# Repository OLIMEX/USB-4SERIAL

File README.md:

# USB-4SERIAL

USB-4SERIAL is Open Source Harrdware USB 2.0 High Speed to four RS232 levels or 3.3V TTL levels serial UARTs and one shared RS485 current loop serial port

## Features
* USB-C High Speed USB 2.0 connector for powering the board and communication
* The serial ports can be with baud rate up to 12Mbps on the TTL connector and up to 115200 bpx on RS232 levels connectors.
* The serial ports are compatible with 16C550 UART and support 5, 6, 7 or 8 data bits and 1 or 2 stop bits, odd, even, none, blank0, mark1 and other parity.
* Supports RTS and CTS hardware automatic flow control for the First one RS232 Serial port.
* Supports half-duplex and RS485 switching for the Fourth port.
* RS485 direction flow selectable by RTS3 or GPIO11
* Reset button
* High reliable industrial grade design -40+85C
* CE-RED and LVD certification
* Four mount holes 3 mm
* PCB dimensions: (150 x 35)mm ~ (5.9 x 1.38)"

Product page: https://www.olimex.com/Products/USB-Modules/USB-4SERIAL/open-source-hardware

## Licensee
* Hardware is released under CERN Open Hardware Licence Version 2 - Strongly Reciprocal, all silkscreen credits to Olimex should remain;
* Software is released under GPL3 Licensee
* Documentation is released under CC BY-SA 3.0

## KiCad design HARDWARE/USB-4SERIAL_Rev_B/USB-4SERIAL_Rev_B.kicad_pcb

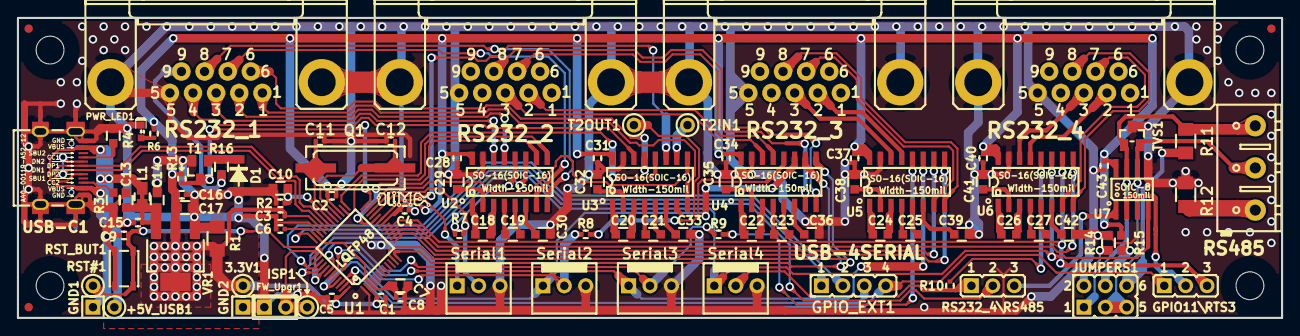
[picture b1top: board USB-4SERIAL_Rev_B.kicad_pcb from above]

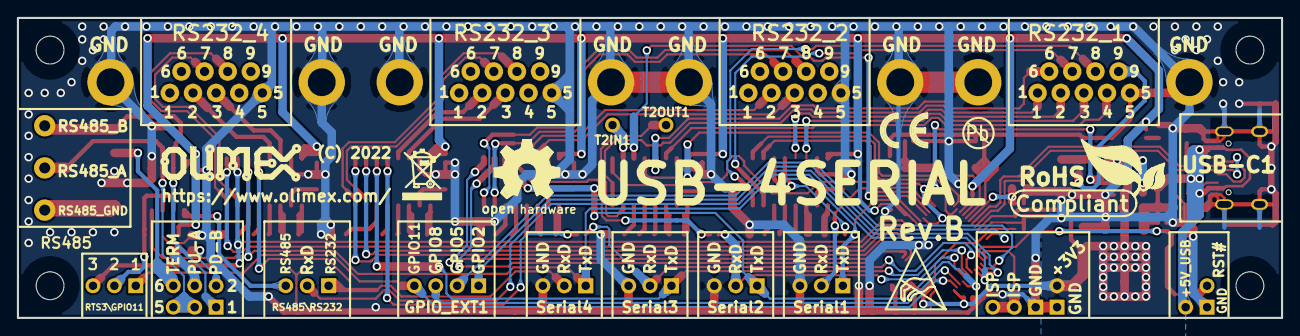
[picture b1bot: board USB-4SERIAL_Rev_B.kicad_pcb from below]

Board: 2 copper layers, 149.9 x 35.6 mm, 111 parts (7 on the bottom side), 104 nets.

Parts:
3.3V1: TESTPAD; TP_PTH-CIRCLE
+5V_USB1: TESTPAD; TP_PTH-CIRCLE
C1, C2, C3, C4, C5, C6, C9, C15, C16, C28, C31, C34, C37, C40, C43: 100nF/10V/10%/X7R/C0402; C_0402_5MIL_DWS
C7: 1uF/10V/10%/X5R/C0603; C_0603_5MIL_DWS
C8: 2.2uF/6.3V/20%/X5R/C0402; C_0402_5MIL_DWS
C10: 20pF/50V/5%/C0G/C0603; C_0603_5MIL_DWS
C11, C12: 39pF/50V/5%/C0G/C0402; C_0402_5MIL_DWS
C13: NA(22uF/6.3V/20%/X5R/C0603); C_0603_5MIL_DWS
C14, C17: 22uF/6.3V/20%/X5R/C0603; C_0603_5MIL_DWS
C18, C19, C20, C21, C22, C23, C24, C25, C26, C27, C29, C30, C32, C33, C35, C36, C38, C39, C41, C42: 100nF/50V/20%/Y5V/C0603; C_0603_5MIL_DWS
D1: 1N5819S4(SOD-123); SOD-123_1C-2A_KA
FID1, FID2, FID3: Fiducial; Fiducial1x3
FW_Upgr1: NA(HN1x2); HN1x2_Jumper
GND1, GND2: TESTPAD; TP_PTH-SQUARE
GPIO11\RTS3: HN1x3(1-2:Opened;2-3:Closed); JP2
GPIO_EXT1: NA(HN1x4); HN1x4
ISP1: TESTPAD; TP_PTH-CIRCLE
JUMPERS1: HN2x3(Closed); HN2x3
L1: NA(FB0805/600R/2A); L_0805_5MIL_DWS
Logo_OLIMEX_SMALL_TB: Logo_OLIMEX_SMALL_TB
Logo_OLIMEX_TB: Logo_OLIMEX_TB
MH1, MH2, MH3, MH4: Mounting_Hole_NPTH; Mounting_Hole_Drill-3.3mm_Clerance-7mm
PWR_LED1: LED/Red/0603; LED_0603_KA
Q1: Q30MHz/20pF/30ppm/2P/HC49-SM(SMD); Q_49U3HMS
R1, R11, R12: 120R/R1206; R_1206_5MIL_DWS
R2, R13: 12k/R0402; R_0402_5MIL_DWS
R3, R4: 5.1k/R0603; R_0603_5MIL_DWS
R6, R7, R8, R9, R10: 330R/R0402; R_0402_5MIL_DWS
R14, R15, R16: 4.7k/R0603; R_0603_5MIL_DWS
RS232_1, RS232_2, RS232_3, RS232_4: DB9_BMR(MALE)
RS232_4\RS485: HN1x3(1-2:Opened;2-3:Closed); JP2
RS485: TB3-5MM(DG306-5.0-03P-12-00AH__DEGSON); TB3-5mm
RST#1: TESTPAD; TP_PTH-CIRCLE
RST_BUT1: YTS-A016-X
Serial1, Serial2, Serial3, Serial4: MK-D-03-LF(WF3S); MK-D-03-LF(WF3S)_(CI3103P1V00_CVILUX)
Sign_Antistatic: Sign_Antistatic
Sign_CE: CE_Sign
Sign_OSHW_8x8: Sign_OSHW_8x8
Sign_PB-Free: Sign_PB-Free
Sign_RecycleBin_1: Sign_RecycleBin_1
Sign_RoHS_1: Sign_RoHS_1
T1: LMUN2211LT1G(SOT-23); SOT23
T2IN1, T2OUT1: TESTPAD; TP_PTH-CIRCLE
TVS1: ESD5302F-3/TR(SOT-23-3); SOT23-3
U1: CH9344L(LQFP-48); LQFP48
U2, U3, U4, U5, U6: ST3232BDR(SO-16); SO-16
U7: YD3082EESA(SOIC-8_150mil); SOIC-8_150mil
USB-C1: USB-C-16P-F(A40-00119-A52-12); USB2.0_TYPE-C(A40-00119-A52-12)
VR1: AMS1117-3.3 (INDUSTRIAL); SOT223

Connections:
+3V3: 3.3V1.1, C1.1, C2.1, C3.1, C4.1, C5.1, C16.2, C17.1, C28.2, C31.2, C34.2, C37.2, C40.2, C43.2, R1.2, R6.1, R13.2, R15.1, U1.2, U1.18, U1.27, U1.33, U1.48, U2.16, U3.16, U4.16, U5.16, U6.16, U7.8, VR1.2
+5V_USB: +5V_USB1.1, C13.1, C14.1, C15.2, L1.1, L1.2, USB-C1.A4, USB-C1.A9, USB-C1.B4, USB-C1.B9, VR1.3
/CC1: R4.2, USB-C1.A5
/CC2: R3.2, USB-C1.B5
/CTS0: U1.26, U2.9
/CTS1: U1.11, U4.9
/CTS2: U1.13, U5.9
/CTS3: U1.15, U6.9
/DCD0: U1.23, U3.9
/DSR0: U1.25, U3.12
/DTE0_CD: RS232_1.1, U3.8
/DTE0_CTS: RS232_1.8, U2.8
/DTE0_DSR: RS232_1.6, U3.13
/DTE0_DTR: RS232_1.4, U3.14
/DTE0_RD: RS232_1.2, U2.13
/DTE0_RI: R16.1, RS232_1.9
/DTE0_RTS: RS232_1.7, U2.7
/DTE0_TD: RS232_1.3, U2.14
/DTE1_CTS: RS232_2.8, U4.8
/DTE1_RD: RS232_2.2, U4.13
/DTE1_RTS: RS232_2.7, U4.7
/DTE1_TD: RS232_2.3, U4.14
/DTE2_CTS: RS232_3.8, U5.8
/DTE2_RD: RS232_3.2, U5.13
/DTE2_RTS: RS232_3.7, U5.7
/DTE2_TD: RS232_3.3, U5.14
/DTE3_CTS: RS232_4.8, U6.8
/DTE3_RD: RS232_4.2, U6.13
/DTE3_RTS: RS232_4.7, U6.7
/DTE3_TD: RS232_4.3, U6.14
/DTR0: U1.21, U3.11
/GPIO2: GPIO_EXT1.1, U1.36
/GPIO5: GPIO_EXT1.2, U1.39
/GPIO8: GPIO_EXT1.3, U1.46
/GPIO11: GPIO11\RTS3.1, GPIO_EXT1.4, U1.47
/ISP: FW_Upgr1.2, ISP1.1, U1.37
/RI0#: R13.1, T1.3, U1.24
/RS485_A: JUMPERS1.3, JUMPERS1.5, RS485.2, TVS1.2, U7.6
/RS485_B: JUMPERS1.1, R11.2, RS485.1, TVS1.1, U7.7
/RS485_GND: R12.2, RS485.3
/RST#: C9.1, RST#1.1, RST_BUT1.2, U1.38
/RSVD1: C10.1, R2.2, U1.30
/RTS0: U1.20, U2.10
/RTS1: U1.12, U4.10
/RTS2: U1.14, U5.10
/RTS3: GPIO11\RTS3.3, U1.16, U6.10
/RXD0: R7.1, Serial1.2, U1.22
/RXD1: R8.1, Serial2.2, U1.44
/RXD2: R9.1, Serial3.2, U1.42
/RXD3: RS232_4\RS485.2, U1.40
/RXD3_RS232: R10.1, RS232_4\RS485.1, Serial4.2
/RXD3_RS485: RS232_4\RS485.3, U7.1
/TXD0: Serial1.1, U1.19, U2.11
/TXD1: Serial2.1, U1.45, U4.11
/TXD2: Serial3.1, U1.43, U5.11
/TXD3: Serial4.1, U1.41, U6.11, U7.4
/V12O: C6.1, C7.1, C8.1, U1.3, U1.35
GND: C1.2, C2.2, C3.2, C4.2, C5.2, C6.2, C7.2, C8.2, C9.2, C10.2, C11.2, C12.2, C13.2, C14.2, C15.1, C16.1, C17.2, C28.1, C29.1, C30.1, C31.1, C32.1, C33.1, C34.1, C35.1, C36.1, C37.1, C38.1, C39.1, C40.1, C41.1, C42.1, C43.1, D1.2, FW_Upgr1.1, GND1.1, GND2.1, PWR_LED1.1, R1.1, R2.1, R3.1, R4.1, R12.1, R14.1, RS232_1.5, RS232_1.G1, RS232_1.G2, RS232_2.5, RS232_2.G1, RS232_2.G2, RS232_3.5, RS232_3.G1, RS232_3.G2, RS232_4.5, RS232_4.G1, RS232_4.G2, RST_BUT1.1, Serial1.3, Serial2.3, Serial3.3, Serial4.3, T1.2, TVS1.3, U1.1, U1.34, U2.15, U3.15, U4.15, U5.15, U6.15, U7.5, USB-C1.0, USB-C1.A1, USB-C1.A12, USB-C1.B1, USB-C1.B12, VR1.1
unnamed: C11.1, Q1.1, U1.29
unnamed: C12.1, Q1.2, U1.28
unnamed: C18.1, U2.1
unnamed: C18.2, U2.3
unnamed: C19.1, U2.4
unnamed: C19.2, U2.5
unnamed: C20.1, U3.1
unnamed: C20.2, U3.3
unnamed: C21.1, U3.4
unnamed: C21.2, U3.5
unnamed: C22.1, U4.1
unnamed: C22.2, U4.3
unnamed: C23.1, U4.4
unnamed: C23.2, U4.5
unnamed: C24.1, U5.1
unnamed: C24.2, U5.3
unnamed: C25.1, U5.4
unnamed: C25.2, U5.5
unnamed: C26.1, U6.1
unnamed: C26.2, U6.3
unnamed: C27.1, U6.4
unnamed: C27.2, U6.5
unnamed: C29.2, U2.2
unnamed: C30.2, U2.6
unnamed: C32.2, U3.2
unnamed: C33.2, U3.6
unnamed: C35.2, U4.2
unnamed: C36.2, U4.6
unnamed: C38.2, U5.2
unnamed: C39.2, U5.6
unnamed: C41.2, U6.2
unnamed: C42.2, U6.6
unnamed: D1.1, R16.2, T1.1
unnamed: GPIO11\RTS3.2, U7.2, U7.3
unnamed: JUMPERS1.2, R14.2
unnamed: JUMPERS1.4, R15.2
unnamed: JUMPERS1.6, R11.1
unnamed: PWR_LED1.2, R6.2
unnamed: R7.2, U2.12
unnamed: R8.2, U4.12
unnamed: R9.2, U5.12
unnamed: R10.2, U6.12
unnamed: T2IN1.1, U3.10
unnamed: T2OUT1.1, U3.7
USB_D+: U1.31, USB-C1.A6, USB-C1.B6
USB_D-: U1.32, USB-C1.A7, USB-C1.B7

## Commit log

2023-05-23 initial upload
2023-05-23 update user manual
2023-05-26 typo removal in user manual

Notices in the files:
HARDWARE/USB-4SERIAL_Rev_B/USB-4SERIAL_Rev_B.kicad_pcb:
(C) 2022
